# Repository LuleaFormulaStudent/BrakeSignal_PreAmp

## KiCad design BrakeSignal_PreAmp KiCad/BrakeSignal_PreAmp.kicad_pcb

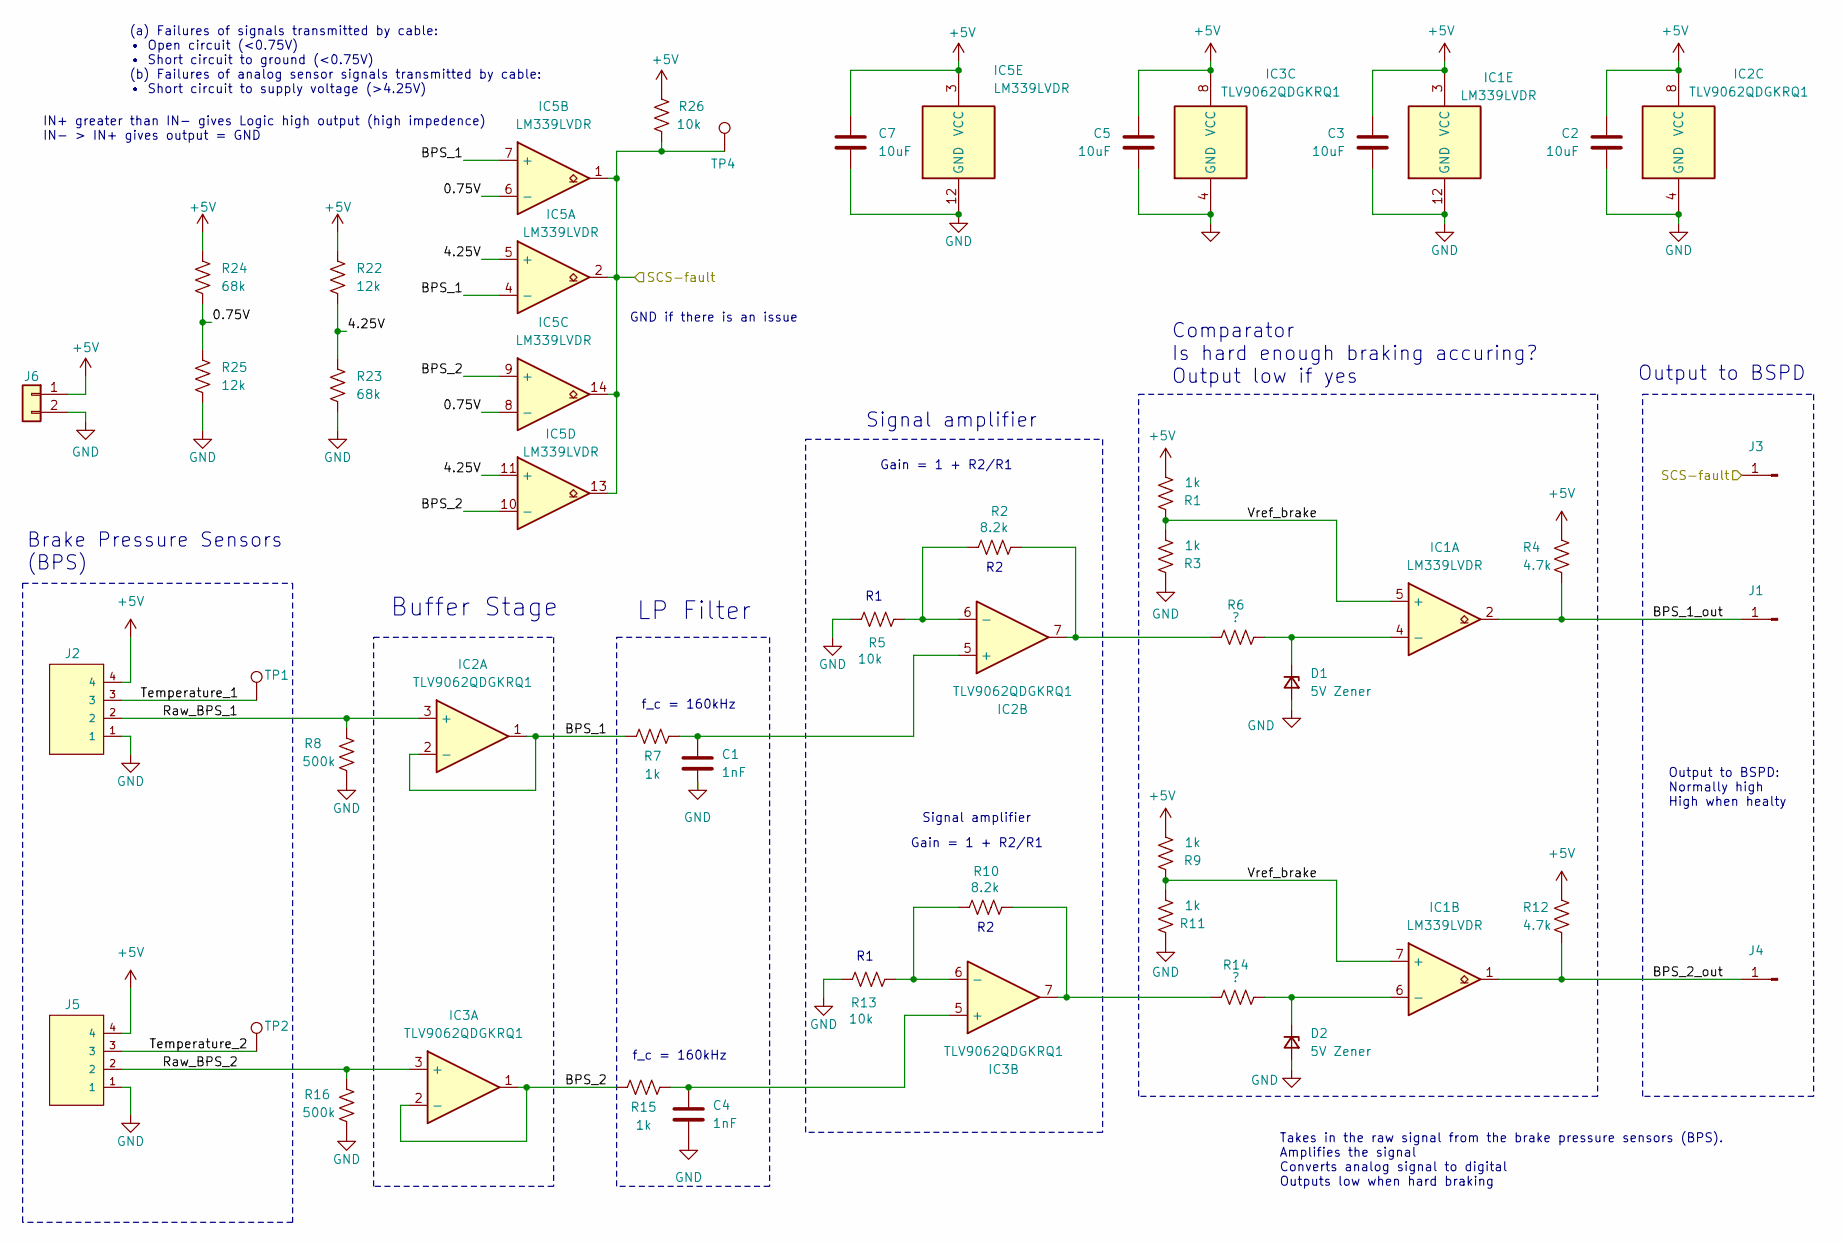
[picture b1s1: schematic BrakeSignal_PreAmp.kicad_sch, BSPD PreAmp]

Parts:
C1, C4: 1nF; C_0805_2012Metric
C2, C3, C5, C7: 10uF; C_0603_1608Metric
D1, D2: 5V Zener
IC1, IC5: LM339LVDR; SOIC127P600X175-14N; Mouser Part Number 595-LM339LVDR
IC2, IC3: TLV9062QDGKRQ1; SOP65P490X110-8N; Mouser Part Number 595-TLV9062QDGKRQ1
J1, J3, J4: Conn_01x01_Pin; PinSocket_1x01_P2.54mm_Vertical
J2, J5: 4P Droit 22-11-2042; JST_XH_B4B-XH-A_1x04_P2.50mm_Vertical; PARTREV BD7; Mouser Part Number 538-22-11-2042
J6: Conn_01x02; JST_XH_B2B-XH-A_1x02_P2.50mm_Vertical
R1, R3, R7, R9, R11, R15: 1k; R_0805_2012Metric
R2, R10: 8.2k; R_0805_2012Metric
R4, R12: 4.7k; R_0805_2012Metric
R5, R13, R26: 10k; R_0805_2012Metric
R6, R14: ?; R_0805_2012Metric
R8, R16: 500k; R_0805_2012Metric
R22, R25: 12k; R_0805_2012Metric
R23, R24: 68k; R_0805_2012Metric
TP1, TP2, TP4: TestPoint; TestPoint_Pad_D1.5mm

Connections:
+5V: C2.1, C3.1, C5.1, C7.1, IC1.3 (VCC), IC2.8 (VCC), IC3.8 (VCC), IC5.3 (VCC), J2.4, J5.4, J6.1, R1.2, R4.1, R9.2, R12.1, R22.1, R24.1, R26.1
/0.75V: IC5.6 (-), IC5.8 (-), R24.2, R25.1
/4.25V: IC5.5 (+), IC5.11 (+), R22.2, R23.1
/BPS_1: IC2.1, IC2.2 (-), IC5.4 (-), IC5.7 (+), R7.1
/BPS_1_out: IC1.2, J1.1, R4.2
/BPS_2: IC3.1, IC3.2 (-), IC5.9 (+), IC5.10 (-), R15.1
/BPS_2_out: IC1.1, J4.1, R12.2
/Raw_BPS_1: IC2.3 (+), J2.2, R8.1
/Raw_BPS_2: IC3.3 (+), J5.2, R16.1
/SCS-fault: IC5.1, IC5.2, IC5.13, IC5.14, J3.1, R26.2, TP4.1
/Temperature_1: J2.3, TP1.1
/Temperature_2: J5.3, TP2.1
/Vref_brake: IC1.5 (+), IC1.7 (+), R1.1, R3.2, R9.1, R11.2
GND: C1.2, C2.2, C3.2, C4.2, C5.2, C7.2, D1.2 (A), D2.2 (A), IC1.12 (GND), IC2.4 (GND), IC3.4 (GND), IC5.12 (GND), J2.1, J5.1, J6.2, R3.1, R5.1, R8.2, R11.1, R13.1, R16.2, R23.2, R25.2
unnamed: D1.1 (K), IC1.4 (-), R6.1
unnamed: D2.1 (K), IC1.6 (-), R14.1
unnamed: IC2.7, R2.2, R6.2
unnamed: C1.1, IC2.5 (+), R7.2
unnamed: IC2.6 (-), R2.1, R5.2
unnamed: IC3.7, R10.2, R14.2
unnamed: C4.1, IC3.5 (+), R15.2
unnamed: IC3.6 (-), R10.1, R13.2

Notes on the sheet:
Brake Pressure Sensors (BPS)
LP Filter
GND if there is an issue
(a) Failures of signals transmitted by cable: • Open circuit (<0.75V) • Short circuit to ground (<0.75V) (b) Failures of analog sensor signals transmitted by cable: • Short circuit to supply voltage (>4.25V)
Gain = 1 + R2/R1
Signal amplifier
Output to BSPD
IN+ greater than IN- gives Logic high output (high impedence) IN- > IN+ gives output = GND
Output to BSPD: Normally high High when healty
Takes in the raw signal from the brake pressure sensors (BPS). Amplifies the signal Converts analog signal to digital Outputs low when hard braking
Buffer Stage
Comparator Is hard enough braking accuring? Output low if yes
f_c = 160kHz

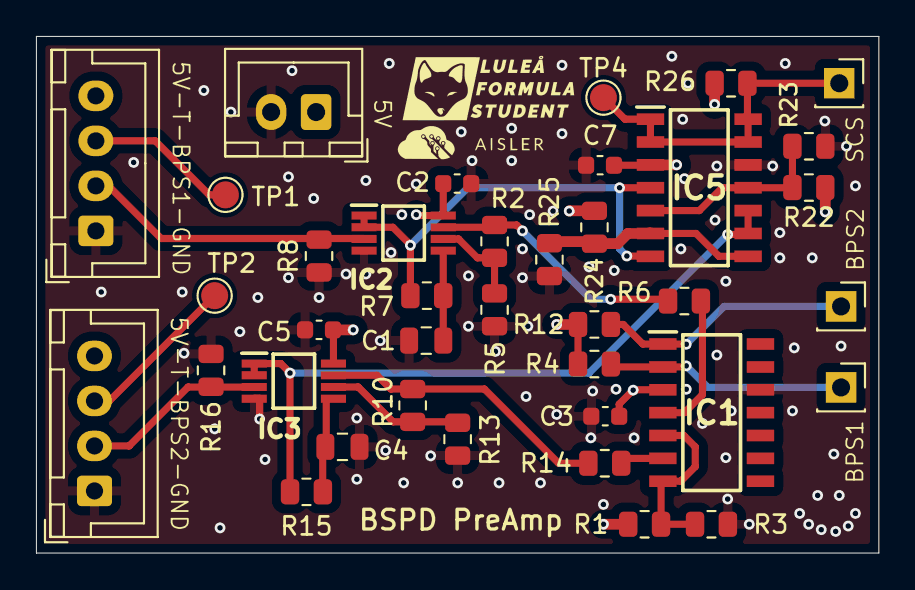
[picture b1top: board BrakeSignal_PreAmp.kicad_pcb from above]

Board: 4 copper layers, 46.8 x 28.7 mm, 38 parts (0 on the bottom side), 22 nets.

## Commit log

2025-05-10 Begun
2025-05-13 Schematic done
2025-05-14 Routing done, no errors. Zener missing
